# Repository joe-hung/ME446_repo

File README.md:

# ME446Spring23
Repository for ME446 Spring 2023 Semester

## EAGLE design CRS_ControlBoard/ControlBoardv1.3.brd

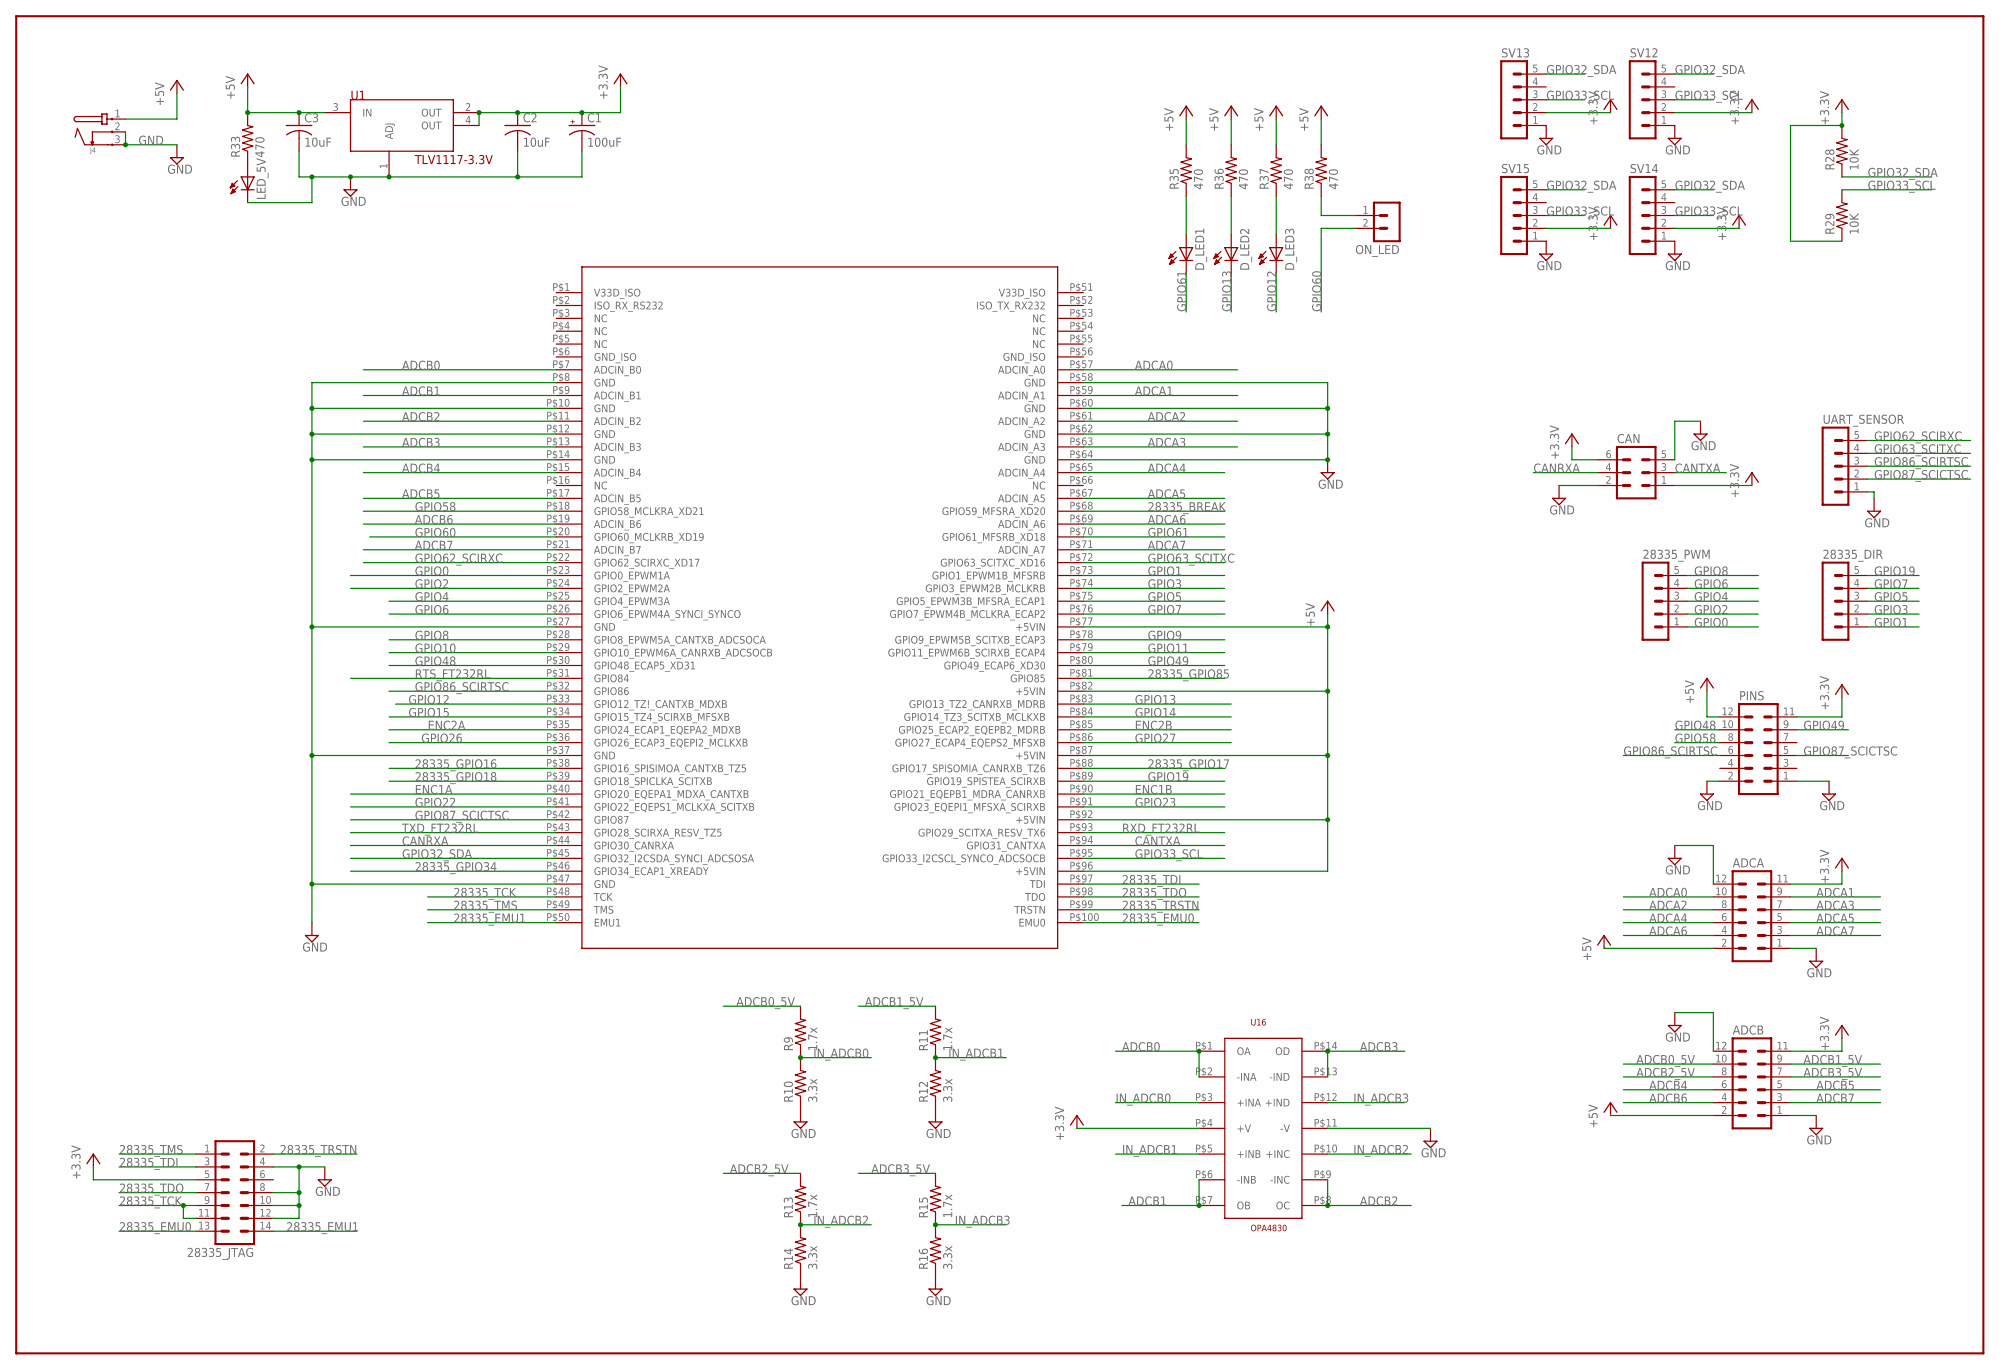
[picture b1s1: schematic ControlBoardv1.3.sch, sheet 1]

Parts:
28335_DIR, 28335_PWM: MA05-1
28335_JTAG: MA07-2
ADCA: MA06-2
ADCB: MA06-2
C1: 100uF; E3,5-8
C2, C3: 10uF; C1206
CAN: MA03-2
D_LED1, D_LED2, D_LED3: LED3MM
J4: JACK-PMS
J7: F28335_CONTROLCARD; MOLEX_DIMM_100
LED_5V: LED3MM
ON_LED: MA02-1
PINS: MA06-2
R9, R11, R13, R15: 1.7x; M1206
R10, R12, R14, R16: 3.3x; M1206
R28, R29: 10K; M1206
R33, R35, R36, R37, R38: 470; M1206
SV12, SV13, SV14, SV15: MA05-1
U1: TLV1117-3.3V; SOT223
U16: OPA4830; OPA4830-TSSOP-14
UART_SENSOR: MA05-1

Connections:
28335_BREAK: J7.P$68 (GPIO59_MFSRA_XD20); also elsewhere on the board
28335_EMU0: 28335_JTAG.13, J7.P$100 (EMU0)
28335_EMU1: 28335_JTAG.14, J7.P$50 (EMU1)
28335_GPIO16: J7.P$38 (GPIO16_SPISIMOA_CANTXB_TZ5); also elsewhere on the board
28335_GPIO17: J7.P$88 (GPIO17_SPISOMIA_CANRXB_TZ6); also elsewhere on the board
28335_GPIO18: J7.P$39 (GPIO18_SPICLKA_SCITXB); also elsewhere on the board
28335_GPIO34: J7.P$46 (GPIO34_ECAP1_XREADY)
28335_GPIO85: J7.P$81 (GPIO85); also elsewhere on the board
28335_TCK: 28335_JTAG.9, 28335_JTAG.11, J7.P$48 (TCK)
28335_TDI: 28335_JTAG.3, J7.P$97 (TDI)
28335_TDO: 28335_JTAG.7, J7.P$98 (TDO)
28335_TMS: 28335_JTAG.1, J7.P$49 (TMS)
28335_TRSTN: 28335_JTAG.2, J7.P$99 (TRSTN)
+3.3V: 28335_JTAG.5, ADCA.11, ADCB.11, C1.+, C2.1, CAN.1, CAN.6, PINS.11, R28.2, R29.1, SV12.2, SV13.2, SV14.2, SV15.2, U1.2 (OUT), U1.4 (OUT), U16.P$4 (+V); also elsewhere on the board
+5V: ADCA.2, ADCB.2, C3.1, J4.1, J7.P$77 (+5VIN), J7.P$82 (+5VIN), J7.P$87 (+5VIN), J7.P$92 (+5VIN), J7.P$96 (+5VIN), PINS.12, R33.2, R35.2, R36.2, R37.2, R38.2, U1.3 (IN); also elsewhere on the board
ADCA0: ADCA.10, J7.P$57 (ADCIN_A0)
ADCA1: ADCA.9, J7.P$59 (ADCIN_A1)
ADCA2: ADCA.8, J7.P$61 (ADCIN_A2)
ADCA3: ADCA.7, J7.P$63 (ADCIN_A3)
ADCA4: ADCA.6, J7.P$65 (ADCIN_A4)
ADCA5: ADCA.5, J7.P$67 (ADCIN_A5)
ADCA6: ADCA.4, J7.P$69 (ADCIN_A6)
ADCA7: ADCA.3, J7.P$71 (ADCIN_A7)
ADCB0: J7.P$7 (ADCIN_B0), U16.P$1 (OA), U16.P$2 (-INA)
ADCB0_5V: ADCB.10, R9.2
ADCB1: J7.P$9 (ADCIN_B1), U16.P$6 (-INB), U16.P$7 (OB)
ADCB1_5V: ADCB.9, R11.2
ADCB2: J7.P$11 (ADCIN_B2), U16.P$8 (OC), U16.P$9 (-INC)
ADCB2_5V: ADCB.8, R13.2
ADCB3: J7.P$13 (ADCIN_B3), U16.P$13 (-IND), U16.P$14 (OD)
ADCB3_5V: ADCB.7, R15.2
ADCB4: ADCB.6, J7.P$15 (ADCIN_B4)
ADCB5: ADCB.5, J7.P$17 (ADCIN_B5)
ADCB6: ADCB.4, J7.P$19 (ADCIN_B6)
ADCB7: ADCB.3, J7.P$21 (ADCIN_B7)
CANRXA: CAN.4, J7.P$44 (GPIO30_CANRXA)
CANTXA: CAN.3, J7.P$94 (GPIO31_CANTXA)
ENC1A: J7.P$40 (GPIO20_EQEPA1_MDXA_CANTXB); also elsewhere on the board
ENC1B: J7.P$90 (GPIO21_EQEPB1_MDRA_CANRXB); also elsewhere on the board
ENC2A: J7.P$35 (GPIO24_ECAP1_EQEPA2_MDXB); also elsewhere on the board
ENC2B: J7.P$85 (GPIO25_ECAP2_EQEPB2_MDRB); also elsewhere on the board
GND: 28335_JTAG.4, 28335_JTAG.8, 28335_JTAG.10, 28335_JTAG.12, ADCA.1, ADCA.12, ADCB.1, ADCB.12, C1.-, C2.2, C3.2, CAN.2, CAN.5, J4.2, J4.3, J7.P$8 (GND), J7.P$10 (GND), J7.P$12 (GND), J7.P$14 (GND), J7.P$27 (GND), J7.P$37 (GND), J7.P$47 (GND), J7.P$58 (GND), J7.P$60 (GND), J7.P$62 (GND), J7.P$64 (GND), LED_5V.K (C), PINS.1, PINS.2, R10.1, R12.1, R14.1, R16.1, SV12.1, SV13.1, SV14.1, SV15.1, U1.1 (ADJ), U16.P$11 (-V), UART_SENSOR.1; also elsewhere on the board
GPIO0: 28335_PWM.1, J7.P$23 (GPIO0_EPWM1A)
GPIO1: 28335_DIR.1, J7.P$73 (GPIO1_EPWM1B_MFSRB)
GPIO2: 28335_PWM.2, J7.P$24 (GPIO2_EPWM2A)
GPIO3: 28335_DIR.2, J7.P$74 (GPIO3_EPWM2B_MCLKRB)
GPIO4: 28335_PWM.3, J7.P$25 (GPIO4_EPWM3A)
GPIO5: 28335_DIR.3, J7.P$75 (GPIO5_EPWM3B_MFSRA_ECAP1)
GPIO6: 28335_PWM.4, J7.P$26 (GPIO6_EPWM4A_SYNCI_SYNCO)
GPIO7: 28335_DIR.4, J7.P$76 (GPIO7_EPWM4B_MCLKRA_ECAP2)
GPIO8: 28335_PWM.5, J7.P$28 (GPIO8_EPWM5A_CANTXB_ADCSOCA)
GPIO9: J7.P$78 (GPIO9_EPWM5B_SCITXB_ECAP3); also elsewhere on the board
GPIO10: J7.P$29 (GPIO10_EPWM6A_CANRXB_ADCSOCB); also elsewhere on the board
GPIO11: J7.P$79 (GPIO11_EPWM6B_SCIRXB_ECAP4); also elsewhere on the board
GPIO12: D_LED3.K (C), J7.P$33 (GPIO12_TZ\!_CANTXB_MDXB)
GPIO13: D_LED2.K (C), J7.P$83 (GPIO13_TZ2_CANRXB_MDRB)
GPIO14: J7.P$84 (GPIO14_TZ3_SCITXB_MCLKXB); also elsewhere on the board
GPIO15: J7.P$34 (GPIO15_TZ4_SCIRXB_MFSXB); also elsewhere on the board
GPIO19: 28335_DIR.5, J7.P$89 (GPIO19_SPISTEA_SCIRXB)
GPIO22: J7.P$41 (GPIO22_EQEPS1_MCLKXA_SCITXB); also elsewhere on the board
GPIO23: J7.P$91 (GPIO23_EQEPI1_MFSXA_SCIRXB); also elsewhere on the board
GPIO26: J7.P$36 (GPIO26_ECAP3_EQEPI2_MCLKXB); also elsewhere on the board
GPIO27: J7.P$86 (GPIO27_ECAP4_EQEPS2_MFSXB); also elsewhere on the board
GPIO32_SDA: J7.P$45 (GPIO32_I2CSDA_SYNCI_ADCSOSA), R28.1, SV12.5, SV13.5, SV14.5, SV15.5
GPIO33_SCL: J7.P$95 (GPIO33_I2CSCL_SYNCO_ADCSOCB), R29.2, SV12.3, SV13.3, SV14.3, SV15.3
GPIO48: J7.P$30 (GPIO48_ECAP5_XD31), PINS.10
GPIO49: J7.P$80 (GPIO49_ECAP6_XD30), PINS.9
GPIO58: J7.P$18 (GPIO58_MCLKRA_XD21), PINS.8
GPIO60: J7.P$20 (GPIO60_MCLKRB_XD19), ON_LED.2
GPIO61: D_LED1.K (C), J7.P$70 (GPIO61_MFSRB_XD18)
GPIO62_SCIRXC: J7.P$22 (GPIO62_SCIRXC_XD17), UART_SENSOR.5; also elsewhere on the board
GPIO63_SCITXC: J7.P$72 (GPIO63_SCITXC_XD16), UART_SENSOR.4; also elsewhere on the board
GPIO86_SCIRTSC: J7.P$32 (GPIO86), PINS.6, UART_SENSOR.3; also elsewhere on the board
GPIO87_SCICTSC: J7.P$42 (GPIO87), PINS.5, UART_SENSOR.2; also elsewhere on the board
IN_ADCB0: R9.1, R10.2, U16.P$3 (+INA)
IN_ADCB1: R11.1, R12.2, U16.P$5 (+INB)
IN_ADCB2: R13.1, R14.2, U16.P$10 (+INC)
IN_ADCB3: R15.1, R16.2, U16.P$12 (+IND)
unnamed: LED_5V.A, R33.1
unnamed: D_LED1.A, R35.1
unnamed: D_LED2.A, R36.1
unnamed: D_LED3.A, R37.1
unnamed: ON_LED.1, R38.1
RTS_FT232RL: J7.P$31 (GPIO84); also elsewhere on the board
RXD_FT232RL: J7.P$93 (GPIO29_SCITXA_RESV_TX6); also elsewhere on the board
TXD_FT232RL: J7.P$43 (GPIO28_SCIRXA_RESV_TZ5); also elsewhere on the board

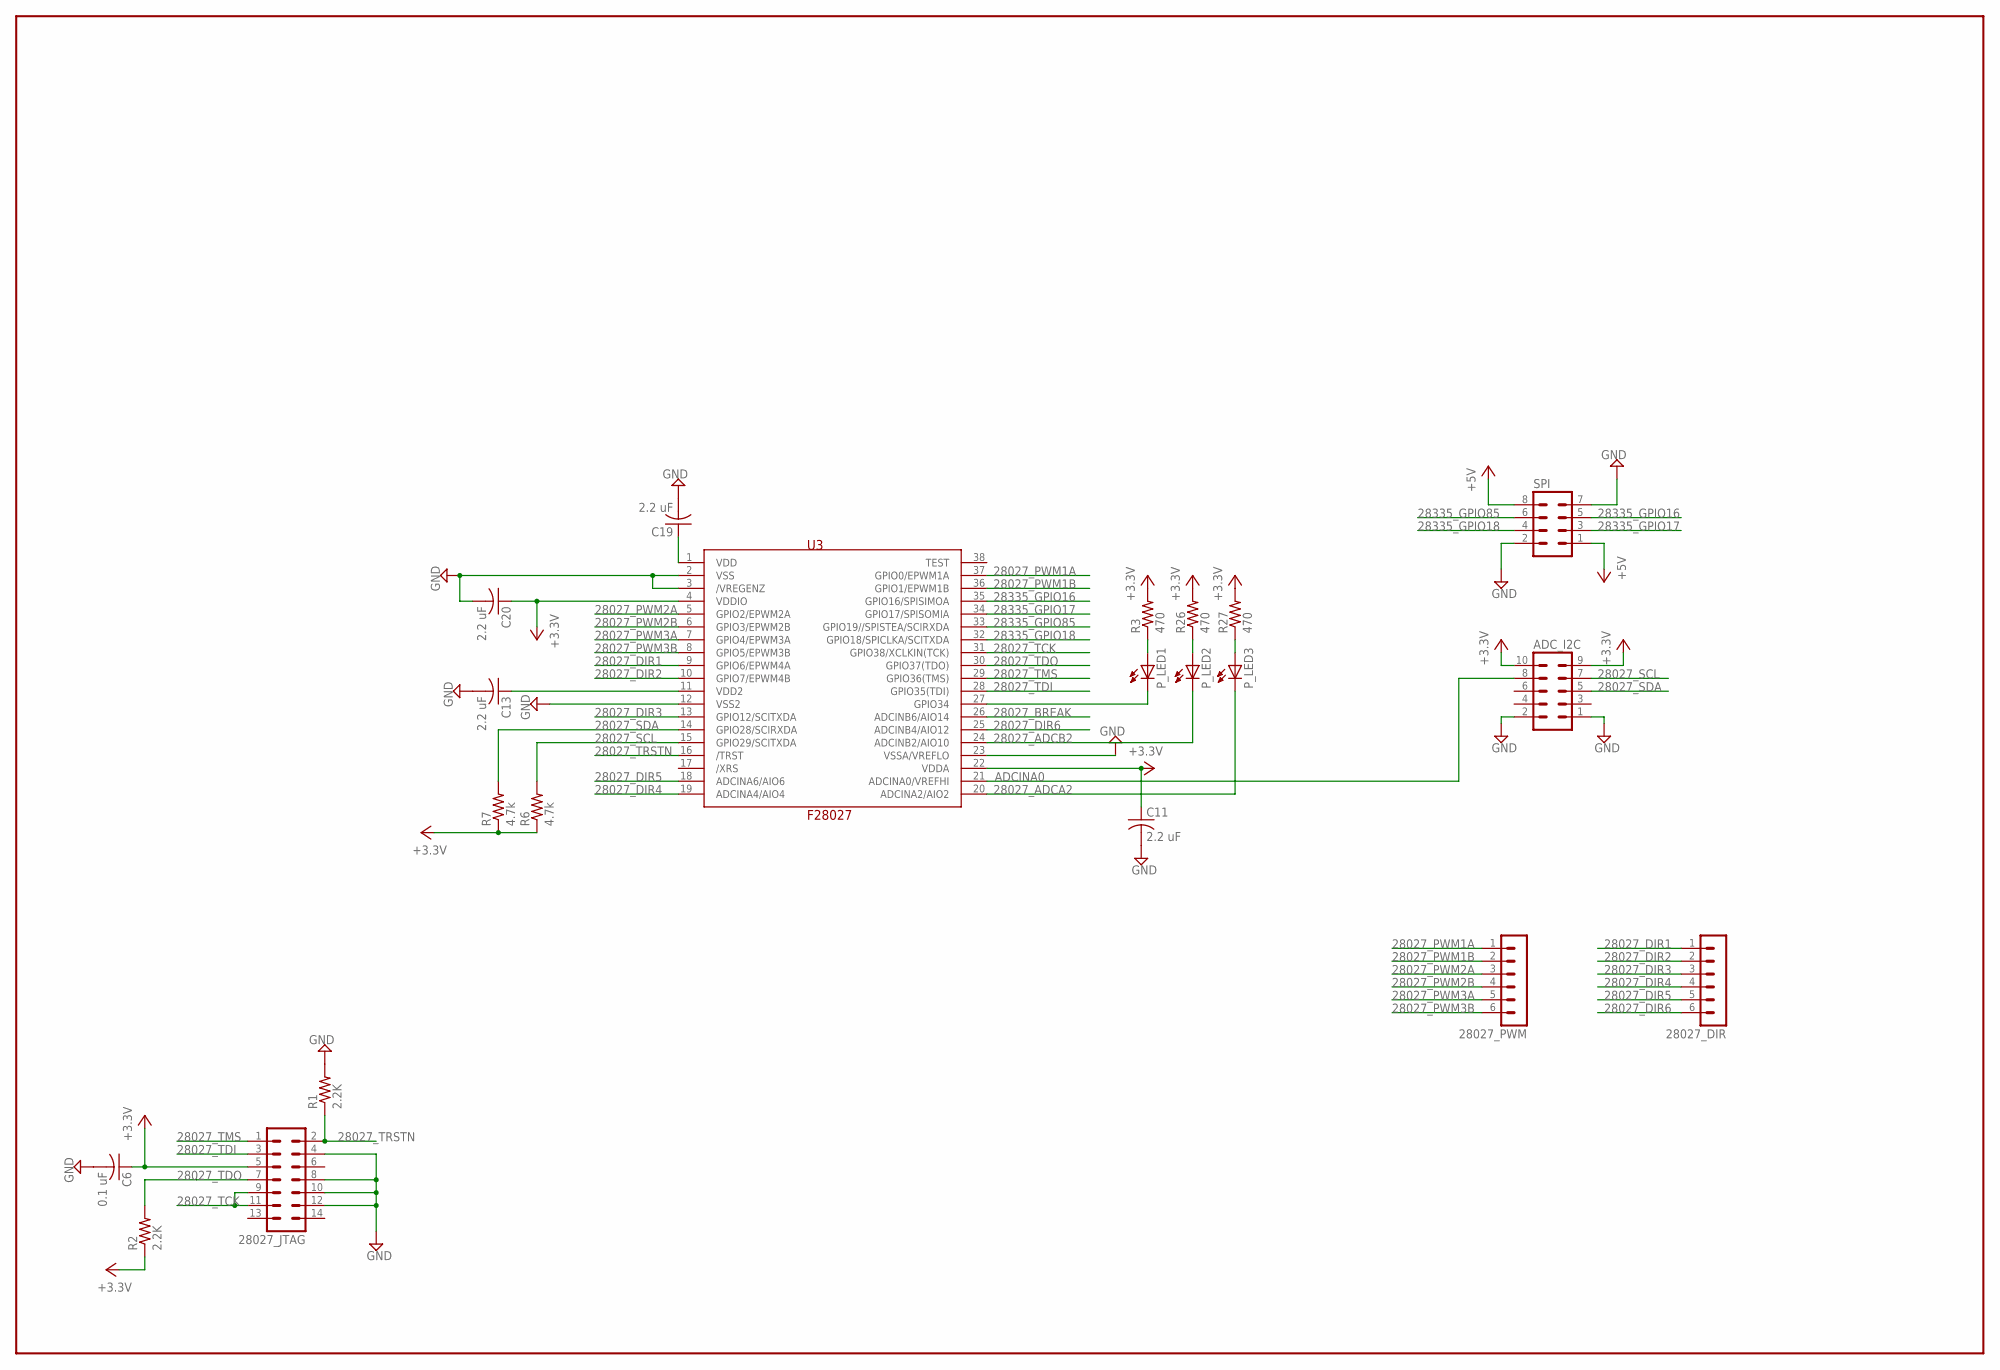
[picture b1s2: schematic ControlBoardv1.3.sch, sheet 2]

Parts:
28027_DIR, 28027_PWM: MA06-1
28027_JTAG: MA07-2
ADC_I2C: MA05-2
C6: 0.1 uF; C1206
C11, C13, C19, C20: 2.2 uF; C1206
P_LED1, P_LED2, P_LED3: LED3MM
R1, R2: 2.2K; M1206
R3, R26, R27: 470; M1206
R6, R7: 4.7k; M1206
SPI: MA04-2
U3: F28027; DA38

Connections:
28027_ADCA2: P_LED3.K (C), U3.20 (ADCINA2/AIO2)
28027_ADCB2: P_LED2.K (C), U3.24 (ADCINB2/AIO10)
28027_BREAK: U3.26 (ADCINB6/AIO14); also elsewhere on the board
28027_DIR1: 28027_DIR.1, U3.9 (GPIO6/EPWM4A)
28027_DIR2: 28027_DIR.2, U3.10 (GPIO7/EPWM4B)
28027_DIR3: 28027_DIR.3, U3.13 (GPIO12/SCITXDA)
28027_DIR4: 28027_DIR.4, U3.19 (ADCINA4/AIO4)
28027_DIR5: 28027_DIR.5, U3.18 (ADCINA6/AIO6)
28027_DIR6: 28027_DIR.6, U3.25 (ADCINB4/AIO12)
28027_GPIO34: P_LED1.K (C), U3.27 (GPIO34)
28027_PWM1A: 28027_PWM.1, U3.37 (GPIO0/EPWM1A)
28027_PWM1B: 28027_PWM.2, U3.36 (GPIO1/EPWM1B)
28027_PWM2A: 28027_PWM.3, U3.5 (GPIO2/EPWM2A)
28027_PWM2B: 28027_PWM.4, U3.6 (GPIO3/EPWM2B)
28027_PWM3A: 28027_PWM.5, U3.7 (GPIO4/EPWM3A)
28027_PWM3B: 28027_PWM.6, U3.8 (GPIO5/EPWM3B)
28027_SCL: ADC_I2C.7, R6.2, U3.15 (GPIO29/SCITXDA)
28027_SDA: ADC_I2C.5, R7.2, U3.14 (GPIO28/SCIRXDA)
28027_TCK: 28027_JTAG.9, 28027_JTAG.11, U3.31 (GPIO38/XCLKIN(TCK))
28027_TDI: 28027_JTAG.3, U3.28 (GPIO35(TDI))
28027_TDO: 28027_JTAG.7, R2.2, U3.30 (GPIO37(TDO))
28027_TMS: 28027_JTAG.1, U3.29 (GPIO36(TMS))
28027_TRSTN: 28027_JTAG.2, R1.1, U3.16 (/TRST)
28335_GPIO16: SPI.5, U3.35 (GPIO16/SPISIMOA); also elsewhere on the board
28335_GPIO17: SPI.3, U3.34 (GPIO17/SPISOMIA); also elsewhere on the board
28335_GPIO18: SPI.4, U3.32 (GPIO18/SPICLKA/SCITXDA); also elsewhere on the board
28335_GPIO85: SPI.6, U3.33 (GPIO19//SPISTEA/SCIRXDA); also elsewhere on the board
+3.3V: 28027_JTAG.5, ADC_I2C.9, ADC_I2C.10, C6.1, C11.1, C20.1, R2.1, R3.2, R6.1, R7.1, R26.2, R27.2, U3.4 (VDDIO), U3.22 (VDDA); also elsewhere on the board
+5V: SPI.1, SPI.8; also elsewhere on the board
ADCINA0: ADC_I2C.8, U3.21 (ADCINA0/VREFHI)
GND: 28027_JTAG.4, 28027_JTAG.8, 28027_JTAG.10, 28027_JTAG.12, ADC_I2C.1, ADC_I2C.2, C6.2, C11.2, C13.2, C19.2, C20.2, R1.2, SPI.2, SPI.7, U3.2 (VSS), U3.3 (/VREGENZ), U3.12 (VSS2), U3.23 (VSSA/VREFLO); also elsewhere on the board
unnamed: C19.1, U3.1 (VDD)
unnamed: C13.1, U3.11 (VDD2)
unnamed: P_LED1.A, R3.1
unnamed: P_LED2.A, R26.1
unnamed: P_LED3.A, R27.1

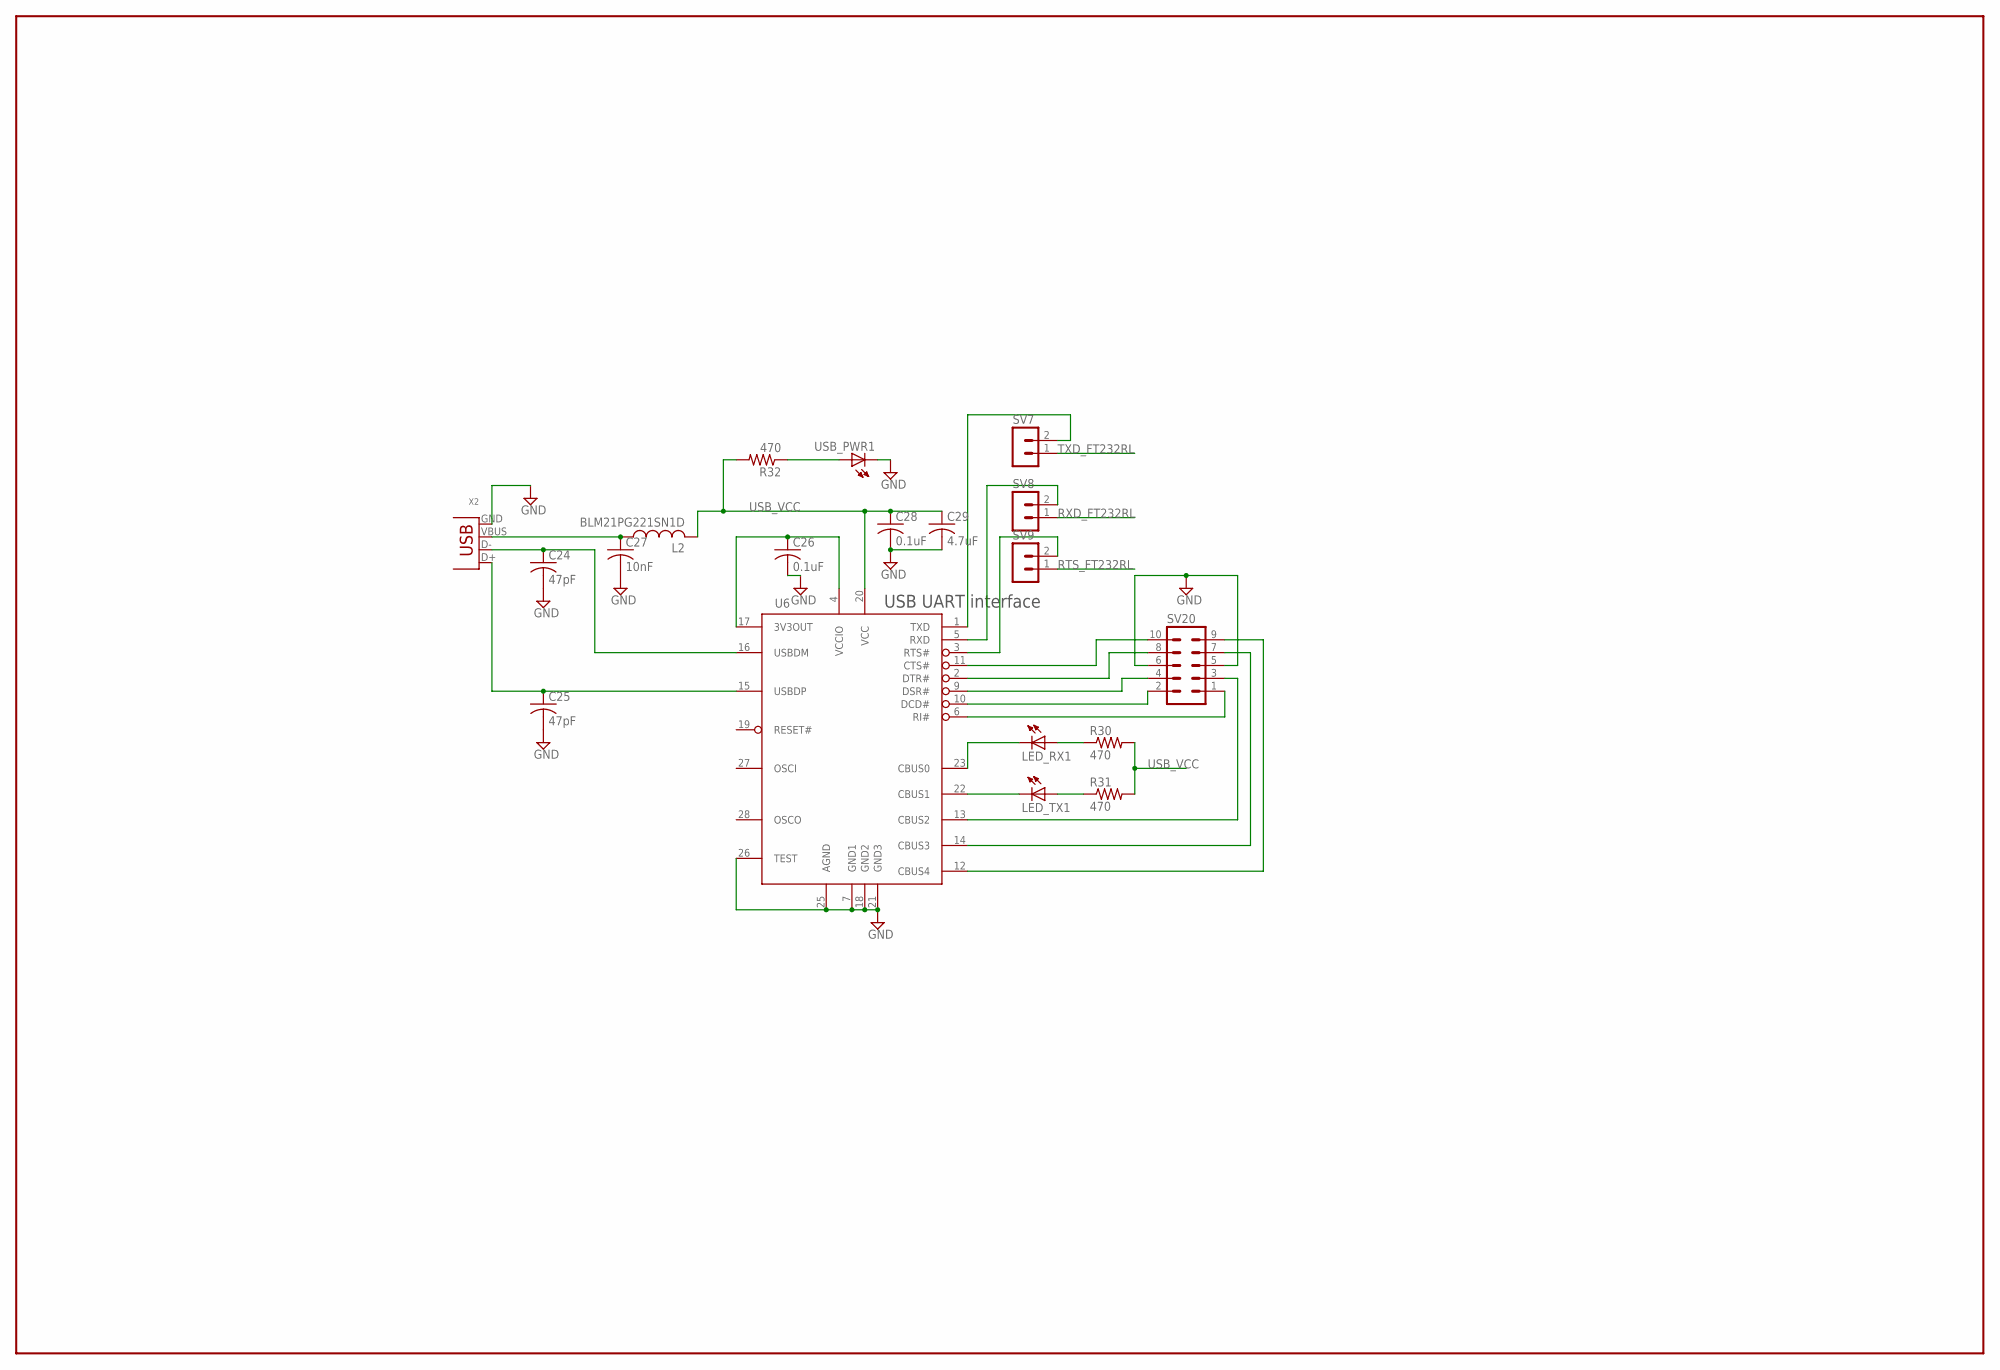
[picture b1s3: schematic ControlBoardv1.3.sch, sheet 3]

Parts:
C24, C25: 47pF; C1206
C26, C28: 0.1uF; C1206
C27: 10nF; C1206
C29: 4.7uF; C1206
L2: BLM21PG221SN1D; L0805
LED_RX1: LED3MM
LED_TX1: LED3MM
R30, R31, R32: 470; M1206
SV7, SV8, SV9: MA02-1
SV20: MA05-2
U6: FT232RL; SSOP28DB
USB_PWR1: LED3MM
X2: USB-B-H

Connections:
GND: C24.2, C25.2, C26.2, C27.2, C28.2, C29.2, SV20.5, SV20.6, U6.7 (GND1), U6.18 (GND2), U6.21 (GND3), U6.25 (AGND), U6.26 (TEST), USB_PWR1.K (C), X2.GND; also elsewhere on the board
unnamed: SV7.2, U6.1 (TXD)
unnamed: SV8.2, U6.5 (RXD)
unnamed: SV9.2, U6.3 (RTS#)
unnamed: C27.1, L2.1, X2.VBUS
unnamed: C24.1, U6.16 (USBDM), X2.D-
unnamed: C25.1, U6.15 (USBDP), X2.D+
unnamed: C26.1, U6.4 (VCCIO), U6.17 (3V3OUT)
unnamed: LED_TX1.K (C), U6.22 (CBUS1)
unnamed: LED_RX1.K (C), U6.23 (CBUS0)
unnamed: LED_RX1.A, R30.1
unnamed: LED_TX1.A, R31.1
unnamed: SV20.10, U6.11 (CTS#)
unnamed: SV20.8, U6.2 (DTR#)
unnamed: SV20.4, U6.9 (DSR#)
unnamed: SV20.2, U6.10 (DCD#)
unnamed: SV20.1, U6.6 (RI#)
unnamed: SV20.3, U6.13 (CBUS2)
unnamed: SV20.7, U6.14 (CBUS3)
unnamed: SV20.9, U6.12 (CBUS4)
unnamed: R32.1, USB_PWR1.A
RTS_FT232RL: SV9.1; also elsewhere on the board
RXD_FT232RL: SV8.1; also elsewhere on the board
TXD_FT232RL: SV7.1; also elsewhere on the board
USB_VCC: C28.1, C29.1, L2.2, R30.2, R31.2, R32.2, U6.20 (VCC)

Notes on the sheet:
USB UART interface

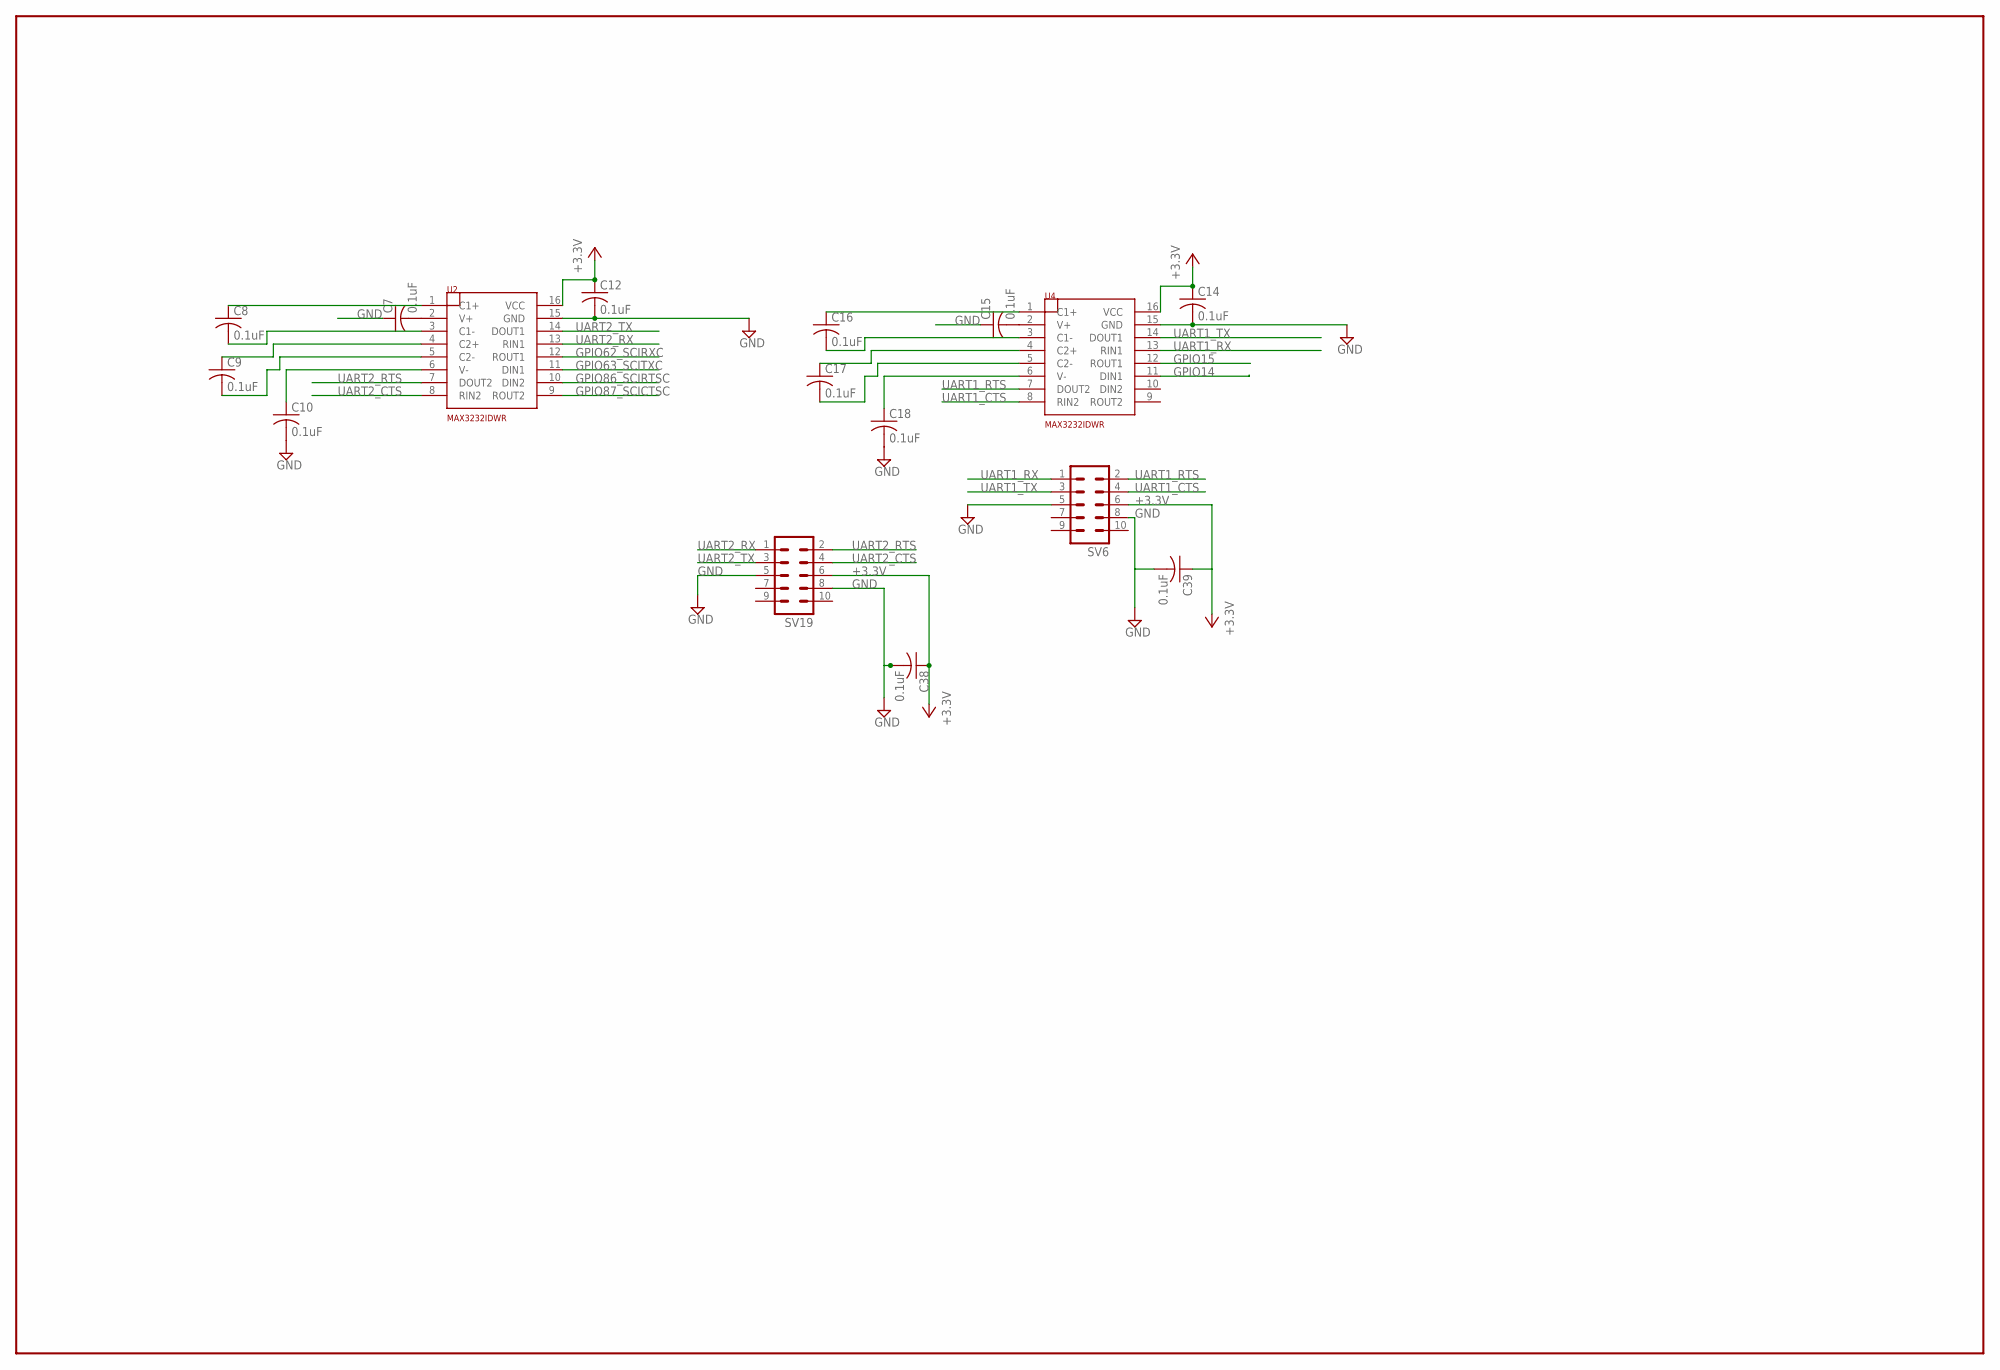
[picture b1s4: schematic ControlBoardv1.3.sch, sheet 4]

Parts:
C7, C8, C9, C10, C12, C14, C15, C16, C17, C18, C38, C39: 0.1uF; C0805K
SV6, SV19: MA05-2
U2, U4: MAX3232IDWR; SO16W

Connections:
+3.3V: C12.1, C14.1, C38.1, C39.1, SV6.6, SV19.6, U2.16 (VCC), U4.16 (VCC); also elsewhere on the board
GND: C7.1, C10.2, C12.2, C14.2, C15.1, C18.2, C38.2, C39.2, SV6.5, SV6.8, SV19.5, SV19.8, U2.15 (GND), U4.15 (GND); also elsewhere on the board
GPIO14: U4.11 (DIN1); also elsewhere on the board
GPIO15: U4.12 (ROUT1); also elsewhere on the board
GPIO62_SCIRXC: U2.12 (ROUT1); also elsewhere on the board
GPIO63_SCITXC: U2.11 (DIN1); also elsewhere on the board
GPIO86_SCIRTSC: U2.10 (DIN2); also elsewhere on the board
GPIO87_SCICTSC: U2.9 (ROUT2); also elsewhere on the board
unnamed: C7.2, U2.2 (V+)
unnamed: C16.1, U4.1 (C1+)
unnamed: C16.2, U4.3 (C1-)
unnamed: C17.1, U4.4 (C2+)
unnamed: C17.2, U4.5 (C2-)
unnamed: C18.1, U4.6 (V-)
unnamed: C15.2, U4.2 (V+)
unnamed: C8.1, U2.1 (C1+)
unnamed: C8.2, U2.3 (C1-)
unnamed: C9.1, U2.4 (C2+)
unnamed: C9.2, U2.5 (C2-)
unnamed: C10.1, U2.6 (V-)
UART1_CTS: SV6.4, U4.8 (RIN2)
UART1_RTS: SV6.2, U4.7 (DOUT2)
UART1_RX: SV6.1, U4.13 (RIN1)
UART1_TX: SV6.3, U4.14 (DOUT1)
UART2_CTS: SV19.4, U2.8 (RIN2)
UART2_RTS: SV19.2, U2.7 (DOUT2)
UART2_RX: SV19.1, U2.13 (RIN1)
UART2_TX: SV19.3, U2.14 (DOUT1)

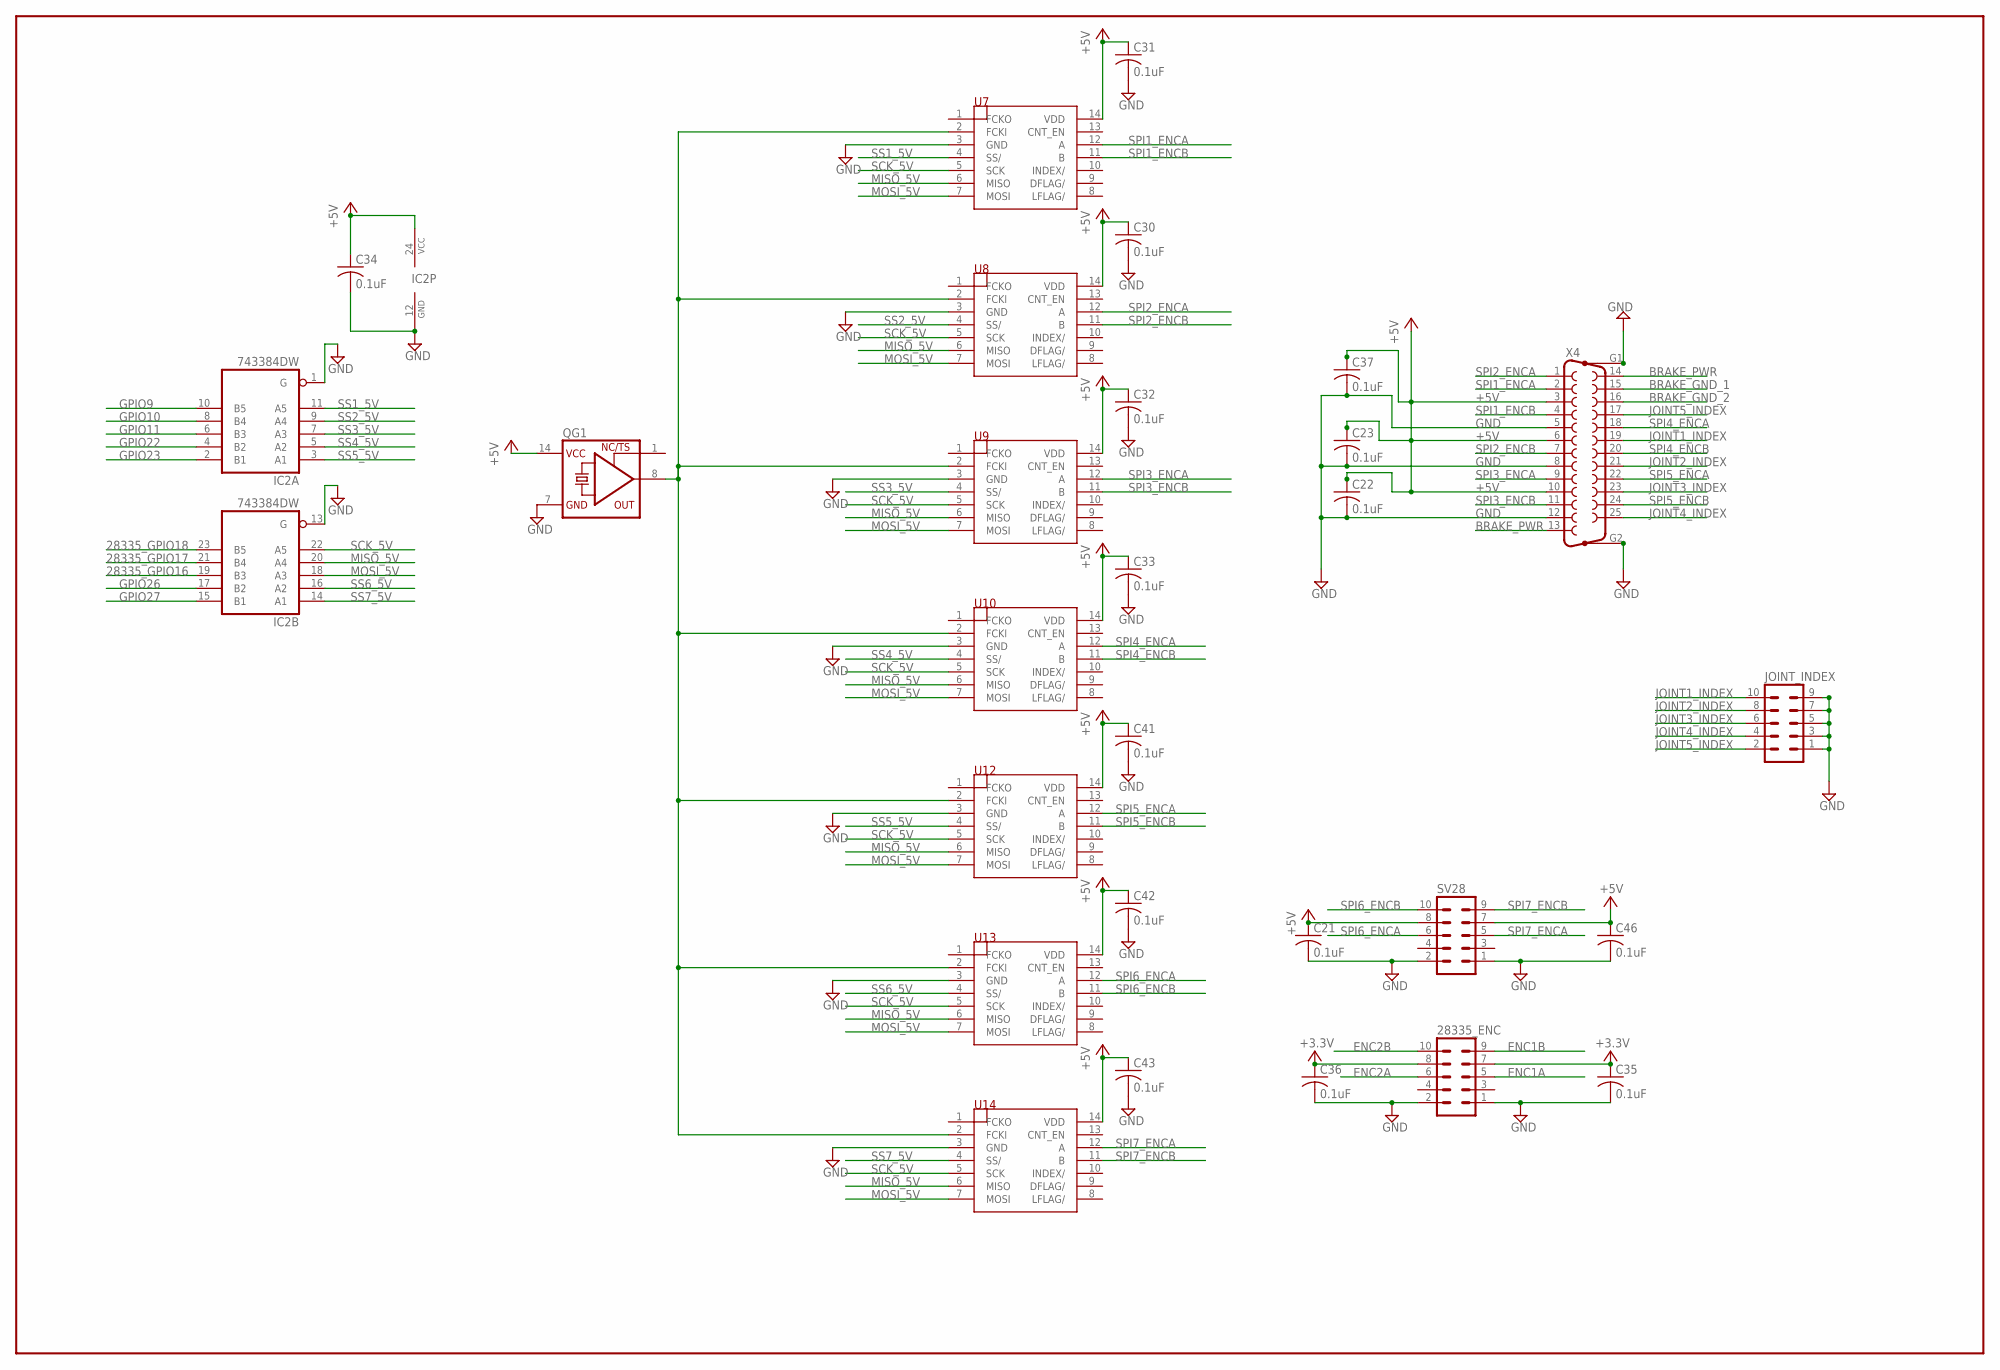
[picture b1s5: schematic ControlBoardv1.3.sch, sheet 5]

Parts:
28335_ENC: MA05-2
C21, C22, C23, C30, C31, C32, C33, C34, C35, C36, C37, C41, C42, C43, C46: 0.1uF; C1206
IC2: 743384DW; SO24W
JOINT_INDEX: MA05-2
QG1: XO-14; DIL14S
SV28: MA05-2
U7, U8, U9, U10, U12, U13, U14: LS7366R; SO14
X4: F25HP

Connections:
28335_GPIO16: IC2.19 (B3); also elsewhere on the board
28335_GPIO17: IC2.21 (B4); also elsewhere on the board
28335_GPIO18: IC2.23 (B5); also elsewhere on the board
+3.3V: 28335_ENC.7, 28335_ENC.8, C35.1, C36.1; also elsewhere on the board
+5V: C21.1, C22.1, C23.1, C30.1, C31.1, C32.1, C33.1, C34.1, C37.1, C41.1, C42.1, C43.1, C46.1, IC2.24 (VCC), QG1.14 (VCC), SV28.7, SV28.8, U7.14 (VDD), U8.14 (VDD), U9.14 (VDD), U10.14 (VDD), U12.14 (VDD), U13.14 (VDD), U14.14 (VDD), X4.3, X4.6, X4.10; also elsewhere on the board
BRAKE_GND_1: X4.15; also elsewhere on the board
BRAKE_GND_2: X4.16; also elsewhere on the board
BRAKE_PWR: X4.13, X4.14; also elsewhere on the board
ENC1A: 28335_ENC.5; also elsewhere on the board
ENC1B: 28335_ENC.9; also elsewhere on the board
ENC2A: 28335_ENC.6; also elsewhere on the board
ENC2B: 28335_ENC.10; also elsewhere on the board
GND: 28335_ENC.1, 28335_ENC.2, C21.2, C22.2, C23.2, C30.2, C31.2, C32.2, C33.2, C34.2, C35.2, C36.2, C37.2, C41.2, C42.2, C43.2, C46.2, IC2.1 (G), IC2.12 (GND), IC2.13 (G), JOINT_INDEX.1, JOINT_INDEX.3, JOINT_INDEX.5, JOINT_INDEX.7, JOINT_INDEX.9, QG1.7 (GND), SV28.1, SV28.2, U7.3 (GND), U8.3 (GND), U9.3 (GND), U10.3 (GND), U12.3 (GND), U13.3 (GND), U14.3 (GND), X4.5, X4.8, X4.12, X4.G1, X4.G2; also elsewhere on the board
GPIO9: IC2.10 (B5); also elsewhere on the board
GPIO10: IC2.8 (B4); also elsewhere on the board
GPIO11: IC2.6 (B3); also elsewhere on the board
GPIO22: IC2.4 (B2); also elsewhere on the board
GPIO23: IC2.2 (B1); also elsewhere on the board
GPIO26: IC2.17 (B2); also elsewhere on the board
GPIO27: IC2.15 (B1); also elsewhere on the board
JOINT1_INDEX: JOINT_INDEX.10, X4.19
JOINT2_INDEX: JOINT_INDEX.8, X4.21
JOINT3_INDEX: JOINT_INDEX.6, X4.23
JOINT4_INDEX: JOINT_INDEX.4, X4.25
JOINT5_INDEX: JOINT_INDEX.2, X4.17
MISO_5V: IC2.20 (A4), U7.6 (MISO), U8.6 (MISO), U9.6 (MISO), U10.6 (MISO), U12.6 (MISO), U13.6 (MISO), U14.6 (MISO)
MOSI_5V: IC2.18 (A3), U7.7 (MOSI), U8.7 (MOSI), U9.7 (MOSI), U10.7 (MOSI), U12.7 (MOSI), U13.7 (MOSI), U14.7 (MOSI)
unnamed: QG1.8 (OUT), U7.2 (FCKI), U8.2 (FCKI), U9.2 (FCKI), U10.2 (FCKI), U12.2 (FCKI), U13.2 (FCKI), U14.2 (FCKI)
SCK_5V: IC2.22 (A5), U7.5 (SCK), U8.5 (SCK), U9.5 (SCK), U10.5 (SCK), U12.5 (SCK), U13.5 (SCK), U14.5 (SCK)
SPI1_ENCA: U7.12 (A), X4.2
SPI1_ENCB: U7.11 (B), X4.4
SPI2_ENCA: U8.12 (A), X4.1
SPI2_ENCB: U8.11 (B), X4.7
SPI3_ENCA: U9.12 (A), X4.9
SPI3_ENCB: U9.11 (B), X4.11
SPI4_ENCA: U10.12 (A), X4.18
SPI4_ENCB: U10.11 (B), X4.20
SPI5_ENCA: U12.12 (A), X4.22
SPI5_ENCB: U12.11 (B), X4.24
SPI6_ENCA: SV28.6, U13.12 (A)
SPI6_ENCB: SV28.10, U13.11 (B)
SPI7_ENCA: SV28.5, U14.12 (A)
SPI7_ENCB: SV28.9, U14.11 (B)
SS1_5V: IC2.11 (A5), U7.4 (SS/)
SS2_5V: IC2.9 (A4), U8.4 (SS/)
SS3_5V: IC2.7 (A3), U9.4 (SS/)
SS4_5V: IC2.5 (A2), U10.4 (SS/)
SS5_5V: IC2.3 (A1), U12.4 (SS/)
SS6_5V: IC2.16 (A2), U13.4 (SS/)
SS7_5V: IC2.14 (A1), U14.4 (SS/)
